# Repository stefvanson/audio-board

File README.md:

# AudioBoard

This project contains the design files for an audio interface board (PCB).

## How to generate the files for JLCPCB

### Generate the gerber files and drill file

- File -> Plot: Select for Front and Bottom (F. and B.) the layers Cu, Mask, Paste and SilkS. Also select the Edge.Cuts layer.
  In that same window at bottom left click "Generate Drill Files..." and generate it.

### Generate the BOM

1. In the schematics editor (Eeschema) click the generate BOM button.
2. Select bom2group_csv and click "Generate".
3. JLCPCB expects the following columns, so adapt the generate CSV file to have these columns (rename and reorder columns):
	- Comment (the "Value" column)
	- Designator (the "Reference" column)
	- Footprint
	- LCSC (the "JLCPCB Part Number" column)

### Generate the pick and place file

1. In the PCB editor click File -> Fabrication Outputs -> Footprint Position (.pos) File.
2. Set the options to generate separate CSV files for the top and bottom and click "Generate Position File".
3. Now open the file and adapt the following column names:
    - Change "Ref" to "Designator"
	- Change "Rot" to "Rotation"
	- Change "Side" to "Layer"
	- Change "PosX" to "Mid X"
	- Change "PosY" to "Mid Y"
4. **Important!** Make sure to check the orientation of all components for which it matters carefully when ordering in JLCPCB!

### Making changes

If you make changes to the schematics you have to:

- Generate the netlist again (AudioBoard.net).
- Generate the BOM again (output/AudioBoard-BOM.csv).
- Load the netlist in the PCB editor and update the PCB with it. Make the required changes.
- Generate the gerber and drill files.
- Check the pick and place file (output/AudioBoard-top-PickAndPlace.csv)

## Known issues / To do list

- [x] MIDI connectors are rotated 180 degrees.
- [x] Fix MIDI Out pin routing (swap pin 4 and 5).
- [x] Fix MIDI Out resistors for 3.3V and change 5V to 3.3V
- [x] Make it more compact.
- [x] Change the footprint of the power connector.
- [x] Test UART
- [x] Connect VDD of Crystal
- [x] Fix I2S_DIN and I2S_DOUT pins (they are connected to the wrong teensy pins).
- [x] Use capacitors with lower voltage ratings
- [x] Add another MIDI output (3.5mm jack)
- [x] Add holes for mounting the PCB in a housing.
- [x] Add holes/pin header for connecting to raspberry Pi
- [x] Align outputs
- [x] Add labels for pin headers.
- [x] Update PCB version number
- [ ] The mounting holes for the Pi Innovo are ground and 3V3 on different sides
      so metal spacers conduct and create a short!

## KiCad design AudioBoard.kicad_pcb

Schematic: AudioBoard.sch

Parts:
C1, C2: 22uF25V; CAPC2012X140N; Manufacturer_Part_Number CL21A226MAQNNNE; Mouser Part Number N/A
IC1: AMS1117-5.0; SOT229P700X180-4N; Manufacturer_Part_Number AMS1117-5.0; JLCPCB Part Number C6187
J1: I2S2_OPT; PinSocket_1x06_P2.54mm_Vertical
J2: SPI_OPT; PinSocket_1x06_P2.54mm_Vertical
J3: Other Teensy pins; PinSocket_1x04_P2.54mm_Vertical
J4: UART_OPT; PinSocket_1x03_P2.54mm_Vertical
J5: 163-179PH-EX; BarrelJack_Horizontal; Mouser Part Number 163-179PH-EX
J12: Raspberry_Pi_2_3; PinHeader_2x20_P2.54mm_Vertical
JP1: Teensy supply select; PinSocket_1x03_P2.54mm_Vertical
U1: Teensy4.0; Teensy40

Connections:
+5V: C2.1, IC1.2 (VOUT), J2.5, J12.2, J12.4, U1.33 (VIN); also elsewhere on the board
/DC_IN: C1.1, J5.A, JP1.1
/I2S2_BCK: J1.3, U1.6 (4_BCLK2)
/I2S2_DIN: J1.2, U1.7 (5_IN2)
/I2S2_DOUT: J1.5, U1.4 (2_OUT2)
/I2S2_LRCK: J1.4, U1.5 (3_LRCLK2)
/I2S_BCK: J12.12, U1.28 (21_A7_RX5_BCLK1); also elsewhere on the board
/I2S_DIN: J12.38, U1.10 (8_TX2_IN1); also elsewhere on the board
/I2S_DOUT: J12.40, U1.9 (7_RX2_OUT1A); also elsewhere on the board
/I2S_LRCK: J12.35, U1.27 (20_A6_TX5_LRCLK1); also elsewhere on the board
/MIDI_IN: J12.10, U1.2 (0_RX1_CRX2_CS1); also elsewhere on the board
/MIDI_OUT: J12.8, U1.3 (1_TX1_CTX2_MISO1); also elsewhere on the board
/MIDI_OUT2: J12.15, U1.24 (17_A3_TX4_SDA1); also elsewhere on the board
/POT1: U1.23 (16_A2_RX4_SCL1); also elsewhere on the board
/POT2: U1.25 (18_A4_SDA0); also elsewhere on the board
/POT3: U1.26 (19_A5_SCL0); also elsewhere on the board
/POT4: U1.29 (22_A8_CTX1); also elsewhere on the board
/POT5: U1.30 (23_A9_CRX1_MCLK1); also elsewhere on the board
/UART_OPT_RX: J4.1, U1.22 (15_A1_RX3_SPDIF_IN)
/UART_OPT_TX: J4.2, U1.21 (14_A0_TX3_SPDIF_OUT)
/V_USB: JP1.3, U1.34 (VUSB)
GND: C1.2, C2.2, IC1.1 (GROUND/ADJUST), J1.1, J2.1, J3.4, J4.3, J5.B, J5.C, J12.6, J12.9, J12.14, J12.20, J12.25, J12.30, J12.34, J12.39, U1.1 (GND), U1.17 (GND), U1.32 (GND); also elsewhere on the board
unnamed: IC1.3 (VIN), JP1.2
unnamed: J2.2, U1.14 (12_MISO_MQSL)
unnamed: J2.3, U1.13 (11_MOSI_CTX1)
unnamed: J2.4, U1.12 (10_CS_MQSR)
unnamed: J3.1, U1.19 (ON_OFF)
unnamed: J3.2, U1.18 (PROGRAM)
unnamed: J3.3, U1.15 (VBAT)

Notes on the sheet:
This dual jump allows selecting between V_USB and DC_IN after cutting the connection between VIN and VUSB on the back of the Teensy
Note that on the Raspberry Pi 3B+ only one UART is available. We have for now connected MIDI_OUT2 in case we would want to implement a software UART using a regular (arbitrarily selected) GPIO pin for now.

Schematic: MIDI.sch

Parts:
D1: SM4007PL; SODFL3718X125N; Manufacturer_Part_Number SM4007PL; JLCPCB Part Number C64898
J13, J14: 57PC5F; Mouser Part Number 502-57PC5F
J16: SJ1-3523N; SJ13523N; Mouser Part Number 490-SJ1-3523N
R6, R10: 33; R_0805_JLCPCB; Manufacturer_Part_Number 0805W8F330JT5E; JLCPCB Part Number C17634
R7, R9: 220; R_0402_JLCPCB; JLCPCB Part Number C25091
R8: 10k; R_0402_JLCPCB; Manufacturer_Part_Number 0402WGF1002TCE; JLCPCB Part Number C25744
R11, R16: 10; R_1206_JLCPCB; Manufacturer_Part_Number 1206W4F100JT5E; JLCPCB Part Number C17903
U2: 6N138SDM; SMDIP-8_W9.53mm; JLCPCB Part Number C188666

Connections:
/MIDI_IN: R9.2, U2.6 (VO2); also elsewhere on the board
/MIDI_OUT: R11.2; also elsewhere on the board
/MIDI_OUT2: R16.2; also elsewhere on the board
GND: J13.6 (GND_1), J13.7 (GND_2), J14.2, J14.6 (GND_1), J14.7 (GND_2), J16.1, R8.2, U2.5 (GND); also elsewhere on the board
unnamed: D1.1, R7.2, U2.2 (C1)
unnamed: D1.2, J13.5, U2.3 (C2)
unnamed: J13.4, R7.1
unnamed: J14.4, R10.1
unnamed: J14.5, R11.1
unnamed: J16.2, R16.1
unnamed: J16.3, R6.1
unnamed: R8.1, U2.7 (VO1)

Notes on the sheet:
3.5mm MIDI outputs following the TRS MIDI Type A pinning

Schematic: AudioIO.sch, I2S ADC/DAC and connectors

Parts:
C3, C4, C11, C12, C13, C18, C20: 10uF6.3V; CAPC1005X70N; Manufacturer_Part_Number CL05A106MQ5NUNC; JLCPCB Part Number C15525
C5, C6: 1uF25V; CAPC1005X60N; Manufacturer_Part_Number CL05A105KA5NQNC; JLCPCB Part Number C52923
C7, C8, C9, C10, C14, C17, C21, C22: 100nF16V; CAPC1005X55N; Manufacturer_Part_Number CL05B104KO5NNNC; JLCPCB Part Number C1525
C15, C16: 10nF50V; CAPC2012X65N; Mouser Part Number N/A
C19, C23: 2.2uF50V; CAPC3216X180N; Manufacturer_Part_Number CL31B225KBHNNNE; Mouser Part Number N/A
C28, C29: 2.2nF50V; CAPC2012X135N; Manufacturer_Part_Number CL21C222JBFNNNE; JLCPCB Part Number C28260
IC2: PCM5102APWR; SOP65P640X120-20N; Mouser Part Number 595-PCM5102APWR
IC3: PCM1803ADBR; SOP65P780X200-20N; Mouser Part Number 595-PCM1803ADBR
J15: RCA_2x2; PJRAS2X2S01X; Mouser Part Number 502-PJRAS2X2S01X
J17: Conn_01x06; PinHeader_1x06_P2.54mm_Vertical
JP2: MODE0; PinSocket_1x02_P2.54mm_Vertical
JP3: MODE1; PinSocket_1x02_P2.54mm_Vertical
JP4: BYPAS; PinSocket_1x02_P2.54mm_Vertical
JP5: OSC_DIS; PinSocket_1x02_P2.54mm_Vertical
R12, R13: 100; R_0805_JLCPCB; JLCPCB Part Number C17408
R14, R15: 470; R_0805_JLCPCB; JLCPCB Part Number C17710
R17: 10k; R_0402_JLCPCB; Manufacturer_Part_Number 0402WGF1002TCE; JLCPCB Part Number C25744
TP1: TestPoint; PinHeader_1x01_P2.54mm_Vertical
U3: 24.576MHz; Crystal_SMD_3225-4Pin_3.2x2.5mm; JLCPCB Part Number C27869

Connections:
+5V: C18.2, IC3.5 (VCC), J17.1; also elsewhere on the board
/Audio IO (I2S)/IN_L: C15.1, IC3.1 (VINL), R12.2
/Audio IO (I2S)/IN_R: C16.2, IC3.2 (VINR), R13.2
/Audio IO (I2S)/JP_BYPAS: IC3.8 (BYPAS), JP4.2
/Audio IO (I2S)/JP_MODE0: IC3.19 (MODE0), JP2.2
/Audio IO (I2S)/JP_MODE1: IC3.20 (MODE1), JP3.2
/Audio IO (I2S)/OUT_L: IC2.6 (OTL), R15.1
/Audio IO (I2S)/OUT_R: IC2.7 (OUTR), R14.1
/Audio IO (I2S)/RCA_IN_L: C5.1, J15.4 (T22)
/Audio IO (I2S)/RCA_IN_R: C6.1, J15.3 (T21)
/Audio IO (I2S)/RCA_OUT_L: C29.1, J15.2 (T12), R15.2
/Audio IO (I2S)/RCA_OUT_R: C28.1, J15.1 (T11), R14.2
/Audio IO (I2S)/SCK: IC3.15 (SCKI), J17.6, TP1.1, U3.3 (OUT); also elsewhere on the board
/I2S_BCK: IC2.13 (BCK), IC3.11 (BCK), J17.5; also elsewhere on the board
/I2S_DIN: IC3.12 (DOUT), J17.4; also elsewhere on the board
/I2S_DOUT: IC2.14 (DIN); also elsewhere on the board
/I2S_LRCK: IC2.15 (LRCK), IC3.10 (LRCK), J17.3; also elsewhere on the board
GND: C3.1, C4.2, C7.2, C8.1, C9.2, C10.2, C11.1, C12.1, C13.1, C14.2, C15.2, C16.1, C17.2, C18.1, C20.1, C21.2, C22.2, C23.1, C28.2, C29.2, IC2.3 (CPGND), IC2.9 (AGND), IC2.10 (DEMP), IC2.11 (FLT), IC2.12 (SCK), IC2.16 (FMT), IC2.19 (GND), IC3.6 (AGND), IC3.9 (TEST), IC3.13 (DGND), IC3.16 (OSR), IC3.18 (FMT1), J15.5 (S1), J15.6 (S2), J17.2, R17.2, U3.2 (GND); also elsewhere on the board
unnamed: C4.1, C8.2, IC2.18 (LDOO)
unnamed: C5.2, R12.1
unnamed: C6.2, R13.1
unnamed: C10.1, C12.2, IC3.3 (VREF1)
unnamed: C17.1, C20.2, IC3.4 (VREF2)
unnamed: C19.1, IC2.2 (CAPP)
unnamed: C19.2, IC2.4 (CAPM)
unnamed: C23.2, IC2.5 (VNEG)

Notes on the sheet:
RCA input
RCA Output
I2S DAC
I2S ADC
Crystal for I2S SCK
Configuration jumpers

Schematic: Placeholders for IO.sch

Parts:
C24, C25, C26, C27, C30: 1uF25V; CAPC1005X60N; Manufacturer_Part_Number CL05A105KA5NQNC; JLCPCB Part Number C52923
J6: EXTRA_POWER; PinSocket_1x03_P2.54mm_Vertical
J7, J8, J9, J10, J11: POT; PinSocket_1x03_P2.54mm_Vertical
R1, R2, R3, R4, R5: 470; R_0805_JLCPCB; JLCPCB Part Number C17710

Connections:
+5V: J6.1; also elsewhere on the board
/POT1: C24.1, R1.1; also elsewhere on the board
/POT2: C26.1, R3.1; also elsewhere on the board
/POT3: C30.1, R5.1; also elsewhere on the board
/POT4: C25.1, R2.1; also elsewhere on the board
/POT5: C27.1, R4.1; also elsewhere on the board
GND: C24.2, C25.2, C26.2, C27.2, C30.2, J6.3, J7.3, J8.3, J9.3, J10.3, J11.3; also elsewhere on the board
unnamed: J7.2, R1.2
unnamed: J8.2, R2.2
unnamed: J9.2, R3.2
unnamed: J10.2, R4.2
unnamed: J11.2, R5.2

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
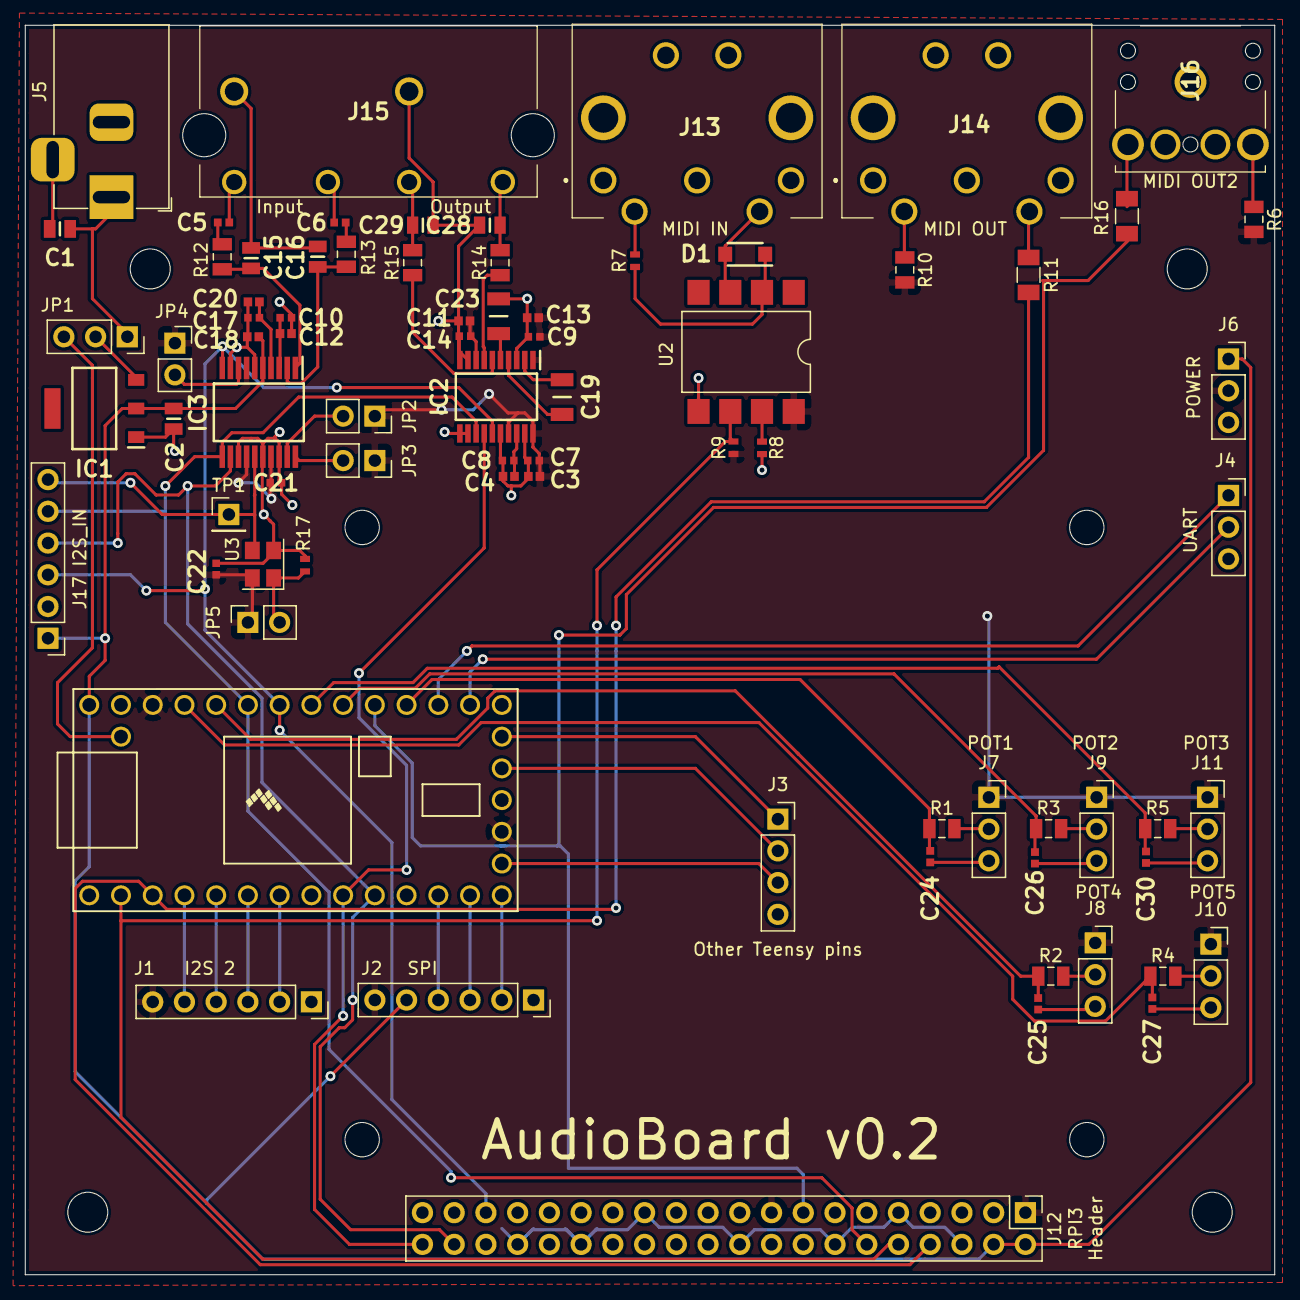
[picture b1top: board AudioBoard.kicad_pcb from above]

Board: 2 copper layers, 100.0 x 100.0 mm, 77 parts (0 on the bottom side), 64 nets.

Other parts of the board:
J17 I2S_IN: Conn_01x06; PinHeader_1x06_P2.54mm_Vertical

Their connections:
+5V: J17 I2S_IN.1; also elsewhere on the board
/Audio IO (I2S)/SCK: J17 I2S_IN.6; also elsewhere on the board
/I2S_BCK: J17 I2S_IN.5; also elsewhere on the board
/I2S_DIN: J17 I2S_IN.4; also elsewhere on the board
/I2S_LRCK: J17 I2S_IN.3; also elsewhere on the board
GND: J17 I2S_IN.2; also elsewhere on the board

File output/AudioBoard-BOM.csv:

Comment,Designator,Footprint,LCSC
10uF6.3V,C12 C20 C18 C11 C13 C4 C3 ,SamacSys_Parts:CAPC1005X70N,C15525
10nF50V,C16 C15 ,SamacSys_Parts:CAPC2012X65N,C1710
2.2uF50V,C19 C23 ,SamacSys_Parts:CAPC3216X180N,C50254
22uF25V,C2 C1 ,SamacSys_Parts:CAPC2012X140N,C45783
100nF16V,C22 C21 C10 C17 C14 C9 C7 C8 ,SamacSys_Parts:CAPC1005X55N,C1525
2.2nF50V,C28 C29 ,SamacSys_Parts:CAPC2012X135N,C28260
1uF25V,C5 C6 C27 C25 C30 C26 C24 ,SamacSys_Parts:CAPC1005X60N,C52923
SM4007PL,D1 ,SamacSys_Parts:SODFL3718X125N,C64898
AMS1117-5.0,IC1 ,SamacSys_Parts:SOT229P700X180-4N,C6187
PCM5102APWR,IC2 ,SamacSys_Parts:SOP65P640X120-20N,C107671
PCM1803ADBR,IC3 ,SamacSys_Parts:SOP65P780X200-20N,C32076
I2S2_OPT,J1 ,Connector_PinSocket_2.54mm:PinSocket_1x06_P2.54mm_Vertical,
Raspberry_Pi_2_3,J12 ,Connector_PinHeader_2.54mm:PinHeader_2x20_P2.54mm_Vertical,
57PC5F,J13 J14 ,SamacSys_Parts:57PC5F,
RCA_2x2,J15 ,SamacSys_Parts:PJRAS2X2S01X,
SJ1-3523N,J16 ,SamacSys_Parts:SJ13523N,
Conn_01x06,J17 ,Connector_PinHeader_2.54mm:PinHeader_1x06_P2.54mm_Vertical,
SPI_OPT,J2 ,Connector_PinSocket_2.54mm:PinSocket_1x06_P2.54mm_Vertical,
Other Teensy pins,J3 ,Connector_PinSocket_2.54mm:PinSocket_1x04_P2.54mm_Vertical,
UART_OPT,J4 ,Connector_PinSocket_2.54mm:PinSocket_1x03_P2.54mm_Vertical,
163-179PH-EX,J5 ,SamacSys_Parts:BarrelJack_Horizontal,
EXTRA_POWER,J6 ,Connector_PinSocket_2.54mm:PinSocket_1x03_P2.54mm_Vertical,
POT,J7 J8 J9 J10 J11 ,Connector_PinSocket_2.54mm:PinSocket_1x03_P2.54mm_Vertical,
Teensy supply select,JP1 ,Connector_PinSocket_2.54mm:PinSocket_1x03_P2.54mm_Vertical,
MODE0,JP2 ,Connector_PinSocket_2.54mm:PinSocket_1x02_P2.54mm_Vertical,
MODE1,JP3 ,Connector_PinSocket_2.54mm:PinSocket_1x02_P2.54mm_Vertical,
BYPAS,JP4 ,Connector_PinSocket_2.54mm:PinSocket_1x02_P2.54mm_Vertical,
OSC_DIS,JP5 ,Connector_PinSocket_2.54mm:PinSocket_1x02_P2.54mm_Vertical,
33,R10 R6 ,SamacSys_Parts:R_0805_JLCPCB,C17634
10,R11 R16 ,SamacSys_Parts:R_1206_JLCPCB,C17903
100,R12 R13 ,SamacSys_Parts:R_0805_JLCPCB,C17408
470,R14 R15 R1 R2 R3 R4 R5 ,SamacSys_Parts:R_0805_JLCPCB,C17710
220,R7 R9 ,SamacSys_Parts:R_0402_JLCPCB,C25091
10k,R8 R17 ,SamacSys_Parts:R_0402_JLCPCB,C25744
TestPoint,TP1 ,Connector_PinHeader_2.54mm:PinHeader_1x01_P2.54mm_Vertical,
Teensy4.0,U1 ,teensy:Teensy40,
6N138SDM,U2 ,Package_DIP:SMDIP-8_W9.53mm,C188666
24.576MHz,U3 ,Crystal:Crystal_SMD_3225-4Pin_3.2x2.5mm,C27869

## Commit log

2020-09-05 Initial version that was ordered AudioBoard v0.1
2020-09-05 Added README with known issues.
2020-09-05 Cleaned up project.
2020-12-27 Updated MIDI schematic and orientation and to do list. Note: Gerber not updated.
2020-12-27 Fixed I2S pins (connected the right ones)
2020-12-27 Updated barreljack (power) footprint and added V_USB selection through jumper.
2020-12-27 Updated I2S crystal/oscillator
2020-12-27 Updated capacitors to smaller/lower voltage ones.
2020-12-27 Replaced one pot by a 3.5mm MIDI Output jack.
2020-12-28 Aligned outputs, started on tracing and connected Pi Innovo header in schematic.
2020-12-29 Updated PCB traces.
2020-12-29 Added mounting holes and wrapped up PCB design.
2020-12-29 Added pin header for I2S input, to connect an external ADC (the PCM1803ADBR was unavailable at the time of ordering).
2021-02-13 Added to do for spacer bug (short due to GND and 3V3 on opposite sides)
